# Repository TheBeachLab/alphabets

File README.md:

<!-- SPDX-FileCopyrightText: 2014-2026 The Beach Lab <https://beachlab.org> -->
<!-- SPDX-License-Identifier: MIT -->
# Alphabets

Welcome to the public repository of the second edition (**V2**) of Alphabets,
an open-source modular split-flap display. Each module shows one character, and
modules can be arranged together to display messages. For information about
the first release from 2014, see [V1](V1). Please also check the [YouTube videos](https://www.youtube.com/playlist?list=PLKDpiLmgp6EuLGCovD-QFxrmyNdrbUmKX)

## The two V2 versions

In this repository you will find two V2 versions: **V2 Prototype** and
**V2 Final**. They are complete, incompatible physical profiles; each has its
own stickers, cards, drum and enclosure, and their parts must not be mixed.

- **V2 Prototype** is for myself. A while ago I printed ten module sticker sets in Dubai and I am using those for prototyping. Of course might use those too. When new V2 Final sticker and card batches are available I will no longer develop this variant.
- **V2 Final** is the supported target for new batches. The expanded character
  map for the German-speaking DACH region (Germany, Austria and Switzerland)
  and Nordic languages requires more vertical artwork space, so this version
  uses taller stickers and cards with a matching drum and enclosure.

See the [V2 physical variants](V2/Hardware/variants/README.md) for the exact parts
and dimensions belonging to each version.

> [!WARNING]
> **UNDER HEAVY DEVELOPMENT — NOT READY FOR USE OR FABRICATION.**
> The V2 Final enclosure has a recorded print check, but the complete mechanism,
> Prototype enclosure, electronics and production process are not physically
> validated. Do not order, print, cut or assemble multiple parts without
> checking the dimensions and validating one complete module. Never mix files
> between the Prototype and Final folders.

## What's new in V2

* 120% pure awesomeness.
* 64 cards with international character set.
* Custom colors: Request custom colored modules and custom characters.
* Build your own or order a kit or ready built module.
* No more gears, direct drive motor
* 3D Printed enclosure
* Entirely designed with widely adopted open source software.
* Assemble in multiple layouts of rows and columns.
* Networked electronics: Connect from one to infinite(*) modules together.
* Web based interface: Control your modules interactively with your web browser.

(*) Not really

## TOC

This table of contents documents V2 Final.

- Mechanical
  - [Cards](doc/cards.md)
  - [Stickers](doc/stickers.md)
  - [Drum](doc/drum.md)
  - [Enclosure](doc/enclosure.md)
- Electronics
  - [Motors](doc/motors.md)
  - [Module Board](doc/module-board.md)
  - [Motherboard](doc/motherboard.md)
  - [Chaining and cables](doc/chaining-and-cables.md)
- Software and Architecture
  - [Protocol](doc/protocol.md)
  - [Module embedded software](doc/module-firmware.md)
  - [Motherboard embedded software](doc/motherboard-firmware.md)
  - [Web interface](doc/web-interface.md)

See the [documentation index](doc/README.md) for the same guide with the
current implementation status of each part.

## License

Except where a file or directory states otherwise, Alphabets' original source
code, firmware, electronics designs, mechanical designs, documentation, and
generated project artifacts are licensed under the [MIT License](LICENSE).
Copyright (c) 2014-2026 [The Beach Lab](https://beachlab.org).

Every commentable file carries a copyright and SPDX license header. JSON,
VS Code workspace, and native KiCad files embed the same fields as document
data so the declaration travels with them. Blender, FreeCAD, OpenType, SVG,
PDF, PNG, JPEG, ZIP, STEP, DXF, binary STL, Gerber, and Excellon files also use
embedded metadata or standard comments and do not need duplicate sidecars.
Only formats without a safely interoperable embedded mechanism use an adjacent
`.license` file. Legacy and bundled third-party sources retain their actual
notices and licenses.

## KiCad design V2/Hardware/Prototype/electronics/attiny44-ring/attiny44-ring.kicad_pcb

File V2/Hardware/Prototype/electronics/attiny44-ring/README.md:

<!-- SPDX-FileCopyrightText: 2014-2026 The Beach Lab <https://beachlab.org> -->
<!-- SPDX-License-Identifier: MIT -->
# Alphabets V2 ATtiny44 SPI-ring module

This directory contains the editable KiCad 10 design for one Alphabets V2
split-flap module. The ATtiny44 participates in the synchronous serial ring
defined in the [prototype module protocol](../../../../Protocol/PROTOCOL_V1_ATTINY44.md)
and drives the four
logic inputs of the external stepper-driver board supplied with the motor.
Its AVR C firmware is in
[`ATtiny44 module firmware`](../../../../Firmware/attiny44-module).

## Circuit

- `U1`: ATtiny44A-SS in SOIC-14.
- `J1`: one 2x3, 2.54 mm, surface-mount chain connector.
- `J5`: one standard 2x3, 2.54 mm, surface-mount AVR ISP connector placed
  immediately below `U1`.
- `J3`: four logic outputs for `IN1` through `IN4` on the external driver.
- `R2`: 10 kOhm reset pull-up in 1206.
- `C1`: 100 nF MCU decoupling capacitor in 1206.
- `C2`: 10 uF bulk capacitor in 1206.
- `JP5`, `JP6`, `JP7`, `JP8`, and `JP16` through `JP25`: 0 Ohm 1206 links
  used as physical copper bridges.

The ATtiny44 signal assignment follows the
[Microchip ATtiny24A/44A/84A data sheet](https://ww1.microchip.com/downloads/en/DeviceDoc/ATtiny24A-44A-84A-DataSheet-DS40002269A.pdf).

## Connectors

| Connector | Pinout |
| --- | --- |
| `J1 CHAIN` | 1 `LATCH`, 2 `CLOCK`, 3 `DATA_IN`, 4 `+5V`, 5 `DATA_OUT`, 6 `GND` |
| `J3 DRIVER` | 1 `IN1`, 2 `IN2`, 3 `IN3`, 4 `IN4` |
| `J5 ISP` | 1 `MISO`, 2 `+5V`, 3 `SCK`, 4 `MOSI`, 5 `RESET`, 6 `GND` |

The chain harness buses pins 1, 2, 4, and 6. It connects pin 5 of each module
to pin 3 of the following module. The external motor-driver board shares the
regulated 5 V supply and ground with this module.

`PB2/HOME` is unconnected on this PCB revision. The firmware uses an explicit
position-0 calibration command and persists completed positions in EEPROM.

## Milling rules

- Board outline: 50 x 50 mm.
- All routed copper is on `F.Cu`.
- Preferred tracks are 20 mil (0.508 mm); compact neckdowns remain 16 mil
  (0.4064 mm), never below the requested 15 mil minimum.
- Routed clearance is 0.40 mm for a 0.40 mm milling bit.
- Corners are native KiCad arcs fitted independently against DRC, trying radius
  limits from 2.00 mm down to 0.20 mm only where the 0.40 mm isolation requires
  it.
- Changes between 20 mil and 16 mil use curved 0.90 mm copper tapers; routed
  SMD pad entries use separate curved copper teardrops.
- Crossings use 0 Ohm 1206 links.
- All discrete SMD passives use 1206 footprints.
- `JP20` through `JP25` use the project-local compact-pitch 3216 crossover
  footprint so their pads fit between the adjacent milled traces.

## Files and validation

- `attiny44-ring.kicad_pro`, `.kicad_sch`, and `.kicad_pcb`: editable native
  KiCad project files.
- `fabrication/`: front-copper Gerbers, drill data, BOM, positions, and STEP.
- `preview/`: rendered top, copper, and schematic views.
- `validation/`: current ERC and DRC/schematic-parity reports.
- `tools/`: deterministic schematic, single-layer routing, organic post-process,
  and design checks.
- `third_party/`: the vendored, licensed geometry engines from
  [KiCad Round Tracks 1.6](https://github.com/mitxela/kicad-round-tracks/releases/tag/1.6)
  and [NilujePerchut's teardrop helper](https://github.com/NilujePerchut/kicad_scripts).

The workflow uses native files and command-line validation rather than GUI
automation. The checked-in Freerouting session reproduces the verified routing
deterministically. Set the KiCad paths, then run:

```sh
make schematic board route organic check fabrication previews
```

`make board route` is the easy-to-edit angular source. `make organic` creates
the fabrication board by fitting 20 mil tracks wherever DRC preserves the full
0.40 mm isolation, retaining 16 mil only where the compact layout requires it.
It then fits the largest safe radius at every corner, adds smooth width tapers
and curved SMD teardrops, and runs the normal ERC/DRC, fabrication, and preview
steps.

Use `make autoroute FREEROUTING_JAR=/path/to/freerouting.jar` only when the
placement or netlist changes and a new routing session must be explored.

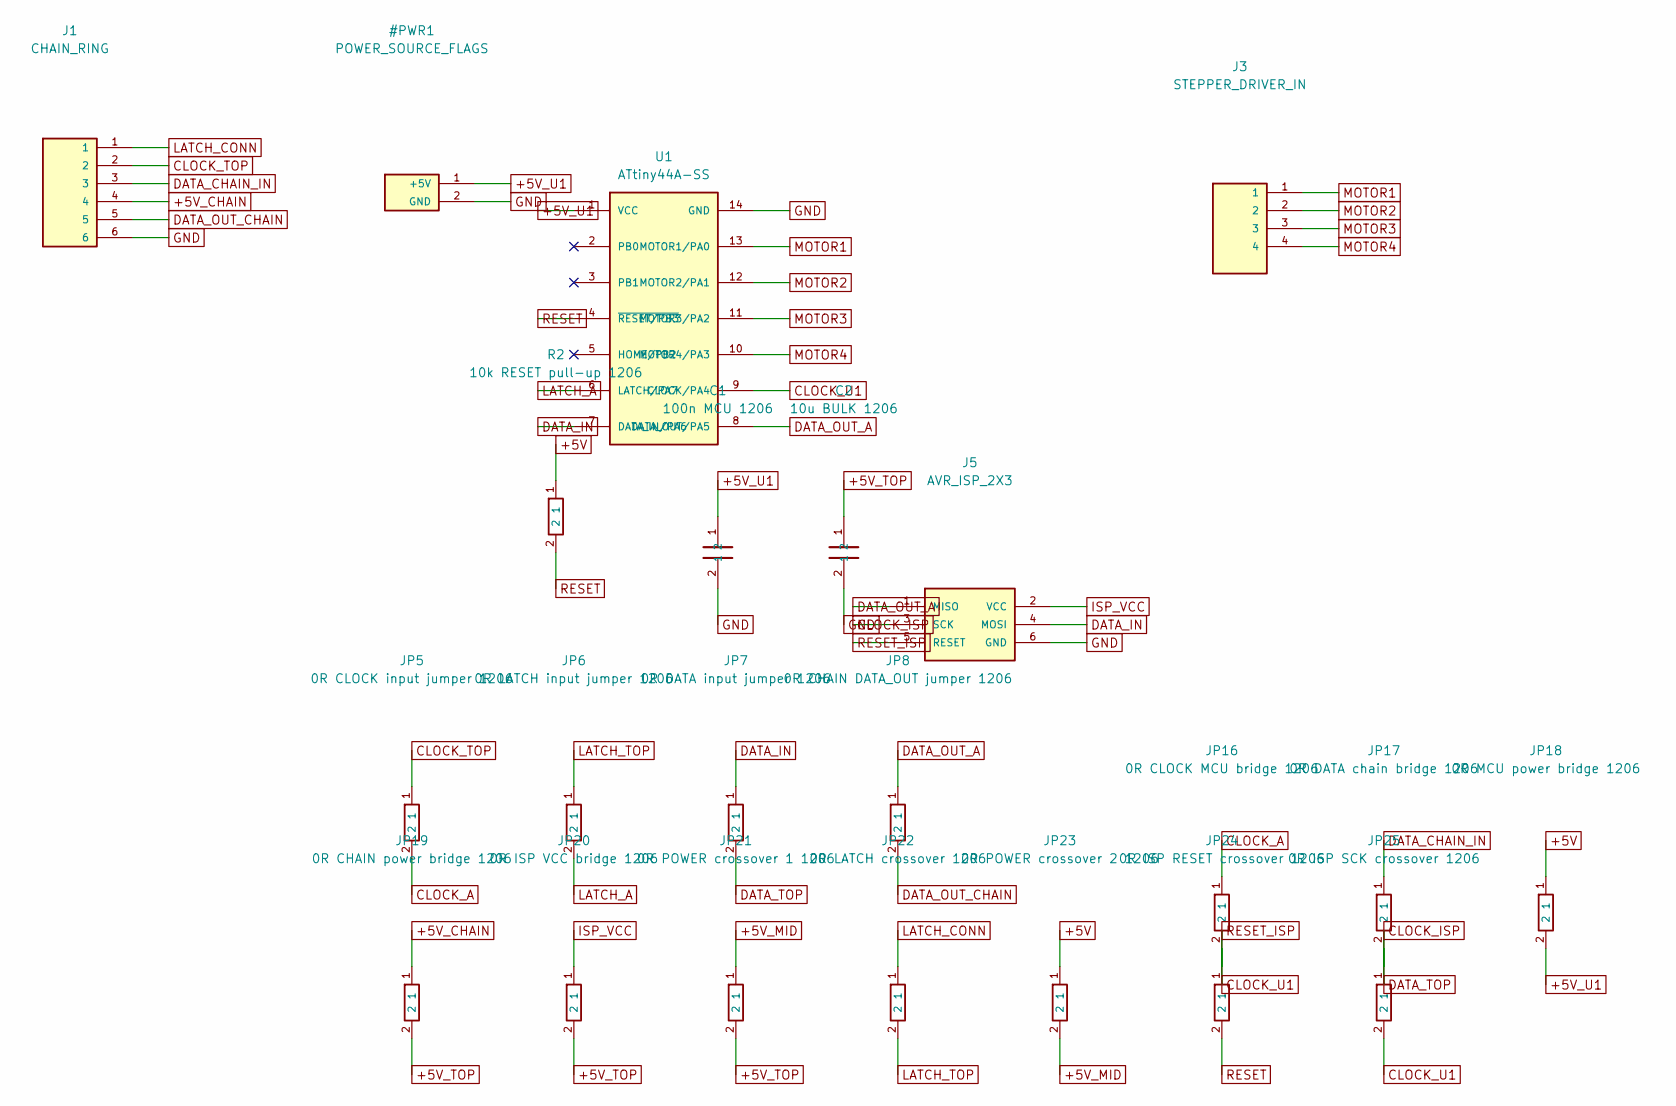
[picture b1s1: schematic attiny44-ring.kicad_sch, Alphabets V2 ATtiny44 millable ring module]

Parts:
C1: 100n MCU 1206; C_1206_3216Metric_Pad1.33x1.80mm_HandSolder
C2: 10u BULK 1206; C_1206_3216Metric_Pad1.33x1.80mm_HandSolder
J1: CHAIN_RING; PinHeader_2x03_P2.54mm_Vertical_SMD
J3: STEPPER_DRIVER_IN; PinHeader_1x04_P2.54mm_Vertical_SMD_Pin1Left
J5: AVR_ISP_2X3; PinHeader_2x03_P2.54mm_Vertical_SMD
JP5: 0R CLOCK input jumper 1206; R_1206_3216Metric_Pad1.30x1.75mm_HandSolder
JP6: 0R LATCH input jumper 1206; R_1206_3216Metric_Pad1.30x1.75mm_HandSolder
JP7: 0R DATA input jumper 1206; R_1206_3216Metric_Pad1.30x1.75mm_HandSolder
JP8: 0R CHAIN DATA_OUT jumper 1206; R_1206_3216Metric_Pad1.30x1.75mm_HandSolder
JP16: 0R CLOCK MCU bridge 1206; R_1206_3216Metric_Pad1.30x1.75mm_HandSolder
JP17: 0R DATA chain bridge 1206; R_1206_3216Metric_Pad1.30x1.75mm_HandSolder
JP18: 0R MCU power bridge 1206; R_1206_3216Metric_Pad1.30x1.75mm_HandSolder
JP19: 0R CHAIN power bridge 1206; R_1206_3216Metric_Pad1.30x1.75mm_HandSolder
JP20: 0R ISP VCC bridge 1206; R_1206_3216Metric_CompactCrossover
JP21: 0R POWER crossover 1 1206; R_1206_3216Metric_CompactCrossover
JP22: 0R LATCH crossover 1206; R_1206_3216Metric_CompactCrossover
JP23: 0R POWER crossover 2 1206; R_1206_3216Metric_CompactCrossover
JP24: 0R ISP RESET crossover 1206; R_1206_3216Metric_CompactCrossover
JP25: 0R ISP SCK crossover 1206; R_1206_3216Metric_CompactCrossover
R2: 10k RESET pull-up 1206; R_1206_3216Metric_Pad1.30x1.75mm_HandSolder
U1: ATtiny44A-SS; SOIC-14_3.9x8.7mm_P1.27mm

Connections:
+5V: JP18.1, JP23.1, R2.1
+5V_CHAIN: J1.4, JP19.1
+5V_MID: JP21.1, JP23.2
+5V_TOP: C2.1, JP19.2, JP20.2, JP21.2
CLOCK_A: JP5.2, JP16.1
CLOCK_ISP: J5.3 (SCK), JP25.1
CLOCK_TOP: J1.2, JP5.1
CLOCK_U1: JP16.2, JP25.2, U1.9 (CLOCK/PA4)
DATA_CHAIN_IN: J1.3, JP17.1
DATA_IN: J5.4 (MOSI), JP7.1, U1.7 (DATA_IN/PA6)
DATA_OUT_A: J5.1 (MISO), JP8.1, U1.8 (DATA_OUT/PA5)
DATA_OUT_CHAIN: J1.5, JP8.2
DATA_TOP: JP7.2, JP17.2
ISP_VCC: J5.2 (VCC), JP20.1
LATCH_A: JP6.2, U1.6 (LATCH/PA7)
LATCH_CONN: J1.1, JP22.1
LATCH_TOP: JP6.1, JP22.2
MOTOR1: J3.1, U1.13 (MOTOR1/PA0)
MOTOR2: J3.2, U1.12 (MOTOR2/PA1)
MOTOR3: J3.3, U1.11 (MOTOR3/PA2)
MOTOR4: J3.4, U1.10 (MOTOR4/PA3)
RESET: JP24.2, R2.2, U1.4 (~RESET/PB3)
RESET_ISP: J5.5 (RESET), JP24.1

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
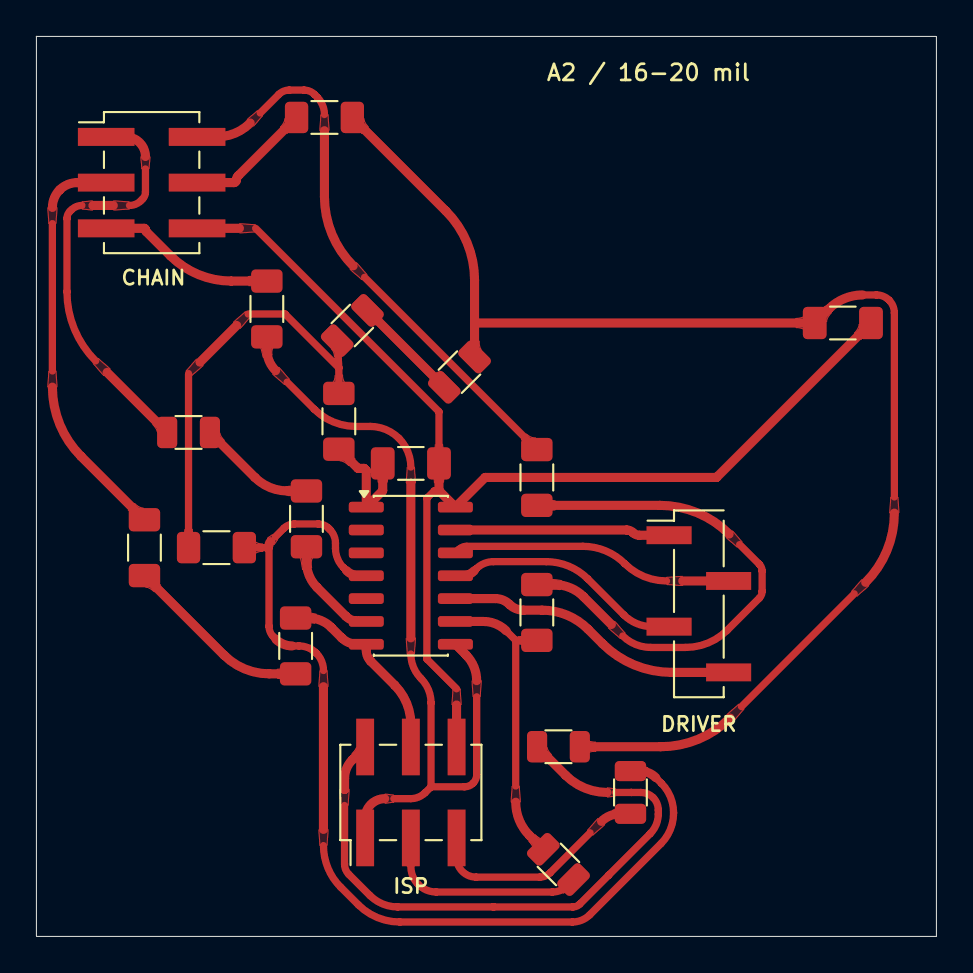
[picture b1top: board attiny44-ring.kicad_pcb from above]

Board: 2 copper layers, 50.0 x 50.0 mm, 21 parts (0 on the bottom side), 25 nets.

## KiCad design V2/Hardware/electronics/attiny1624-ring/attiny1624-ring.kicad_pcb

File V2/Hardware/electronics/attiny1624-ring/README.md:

<!-- SPDX-FileCopyrightText: 2014-2026 The Beach Lab <https://beachlab.org> -->
<!-- SPDX-License-Identifier: MIT -->
# Alphabets V2 ATtiny1624 ring module

This directory contains the editable KiCad 10 design for one Alphabets V2
split-flap module. The board keeps the existing 2x3 synchronous-ring connector,
drives an external four-input stepper board, reads a powered HOME sensor, and
uses the ATtiny1624's one-wire UPDI programming interface.

The hardware assignment follows Microchip's
[ATtiny1624/1626/1627 data sheet](https://ww1.microchip.com/downloads/en/DeviceDoc/ATtiny1624-26-27-DataSheet-DS40002234B.pdf).
Microchip documents PA0 as UPDI/RESET and PA1, PA2, and PA3 as SPI0 MOSI, MISO,
and SCK respectively. The standard programming connection is the 2x3,
2.54 mm UPDI header described in Microchip's
[UPDI connection guide](https://onlinedocs.microchip.com/oxy/GUID-ACE76F82-8072-410B-AFA7-16B2BF7B4CBA-en-US-8/GUID-C59C16EC-2784-4583-8198-2780FE485FFC.html).

## Circuit

- `U1`: ATtiny1624-SSU in SOIC-14.
- `J1`: 2x3 SMD ring connector for LATCH, CLOCK, serial data, +5 V, and GND.
- `J3`: four logic outputs for the external stepper driver.
- `J4`: powered three-pin HOME sensor connector with a 10 kOhm pull-up.
- `J5`: 2x3 SMD UPDI connector; pins 1, 2, and 6 carry UPDI, target VDD, and
  GND. Pins 3 through 5 are intentionally not connected.
- `R1`: 10 kOhm UPDI pull-up; `R2`: 10 kOhm HOME pull-up.
- `C1`: 100 nF local MCU decoupling; `C2`: 1 nF high-frequency bypass;
  `C3`: 10 uF board bulk capacitance.
- `JP1` through `JP4`, `JP6`, and `JP9`: removable 0 Ohm 1206
  links that partition power, ground, and ring signals for assembly and
  diagnosis.

The board defines this ATtiny1624 signal assignment:

| Function | MCU signal | Physical pin |
| --- | --- | ---: |
| VDD | `VDD` | 1 |
| LATCH | `PA4 / SPI0 SS` | 2 |
| HOME | `PA5` | 3 |
| Motor 4 | `PB3` | 6 |
| Motor 3 | `PB2` | 7 |
| Motor 2 | `PB1` | 8 |
| Motor 1 | `PB0` | 9 |
| UPDI | `PA0 / UPDI` | 10 |
| DATA_IN | `PA1 / SPI0 MOSI` | 11 |
| DATA_OUT | `PA2 / SPI0 MISO` | 12 |
| CLOCK | `PA3 / SPI0 SCK` | 13 |
| GND | `GND` | 14 |

`PA6` and `PA7` remain available and are intentionally not connected in this
revision. The matching firmware and host-side protocol tests are in
[`../../../Firmware/attiny1624-module`](../../../Firmware/attiny1624-module).

## Connectors

| Connector | Pinout |
| --- | --- |
| `J1 CHAIN` | 1 `LATCH`, 2 `CLOCK`, 3 `DATA_IN`, 4 `+5V`, 5 `DATA_OUT`, 6 `GND` |
| `J3 DRIVER` | 1 `MOTOR1`, 2 `MOTOR2`, 3 `MOTOR3`, 4 `MOTOR4` |
| `J4 HOME` | 1 `+5V`, 2 `HOME`, 3 `GND` |
| `J5 UPDI` | 1 `UPDI`, 2 target `VDD`, 3-5 NC, 6 `GND` |

The chain connector follows [`../../../PROTOCOL.md`](../../../PROTOCOL.md):
pins 1, 2, 4, and 6 are bused, while pin 5 of one module feeds pin 3 of the
next module.

## Single-sided construction

- Finished outline: 50 x 50 mm.
- All routed copper is on `F.Cu`; the design contains no vias or back-copper
  tracks.
- Preferred tracks are 20 mil (0.508 mm). Constrained neckdowns are 16 mil
  (0.4064 mm), above the 15 mil minimum.
- Copper clearance is 0.40 mm for a 0.40 mm milling tool.
- Corners use native KiCad arcs with adaptive radii from 0.20 to 2.00 mm.
- Width transitions use curved copper tapers and routed SMD entries use curved
  teardrops.
- Every discrete resistor and capacitor uses a hand-solderable 1206 footprint.

Ten insulated wire links cross above the routed copper. Solder insulated wire
between the two pads of each footprint; the dashed `F.Fab` line marks its
assembly path and is not copper:

| Reference | Signal | Pad spacing |
| --- | --- | ---: |
| `JP5` | CLOCK | 22.3 mm |
| `JP7` | DATA_IN | 25.6 mm |
| `JP8` | DATA_OUT | 23.5 mm |
| `JP10` | UPDI | 16.6 mm |
| `JP11` | chain GND | 29.7 mm |
| `JP12` | motor phase 3 | 23.5 mm |
| `JP13` | MCU power source | 17.7 mm |
| `JP14` | motor phase 1 | 30.3 mm |
| `JP15` | motor phase 2 | 24.5 mm |
| `JP16` | main power distribution | 27.0 mm |

## Files and reproducible validation

- `attiny1624-ring.kicad_pro`, `.kicad_sch`, and `.kicad_pcb`: editable
  native KiCad project files.
- `fabrication/`: Gerbers, drill outputs, BOM, positions, and STEP model.
- `preview/`: top render, front-copper drawing, and schematic drawing.
- `validation/`: ERC and DRC/schematic-parity reports.
- `routing/attiny1624-ring.ses`: checked-in single-layer routing session.
- `tools/`: deterministic generators, route import, organic post-processing,
  and project-specific electrical/mechanical checks.

The normal reproducible path starts from the checked-in route:

```sh
make schematic board route organic check fabrication previews
```

Set `KICAD_CLI`, `KICAD_PYTHON`, `KIUTILS_PYTHON`, and
`KICAD10_FOOTPRINT_DIR` for the installed KiCad environment. When placement or
the netlist changes, create a new session with:

```sh
make autoroute FREEROUTING_JAR=/path/to/freerouting.jar
```

`make check` enforces the 50 x 50 mm outline, front-copper-only routing, zero
vias, 16/20 mil widths, ten wire links, native arcs, teardrops, zero ERC/DRC
violations, zero unrouted connections, and exact schematic-to-PCB parity.

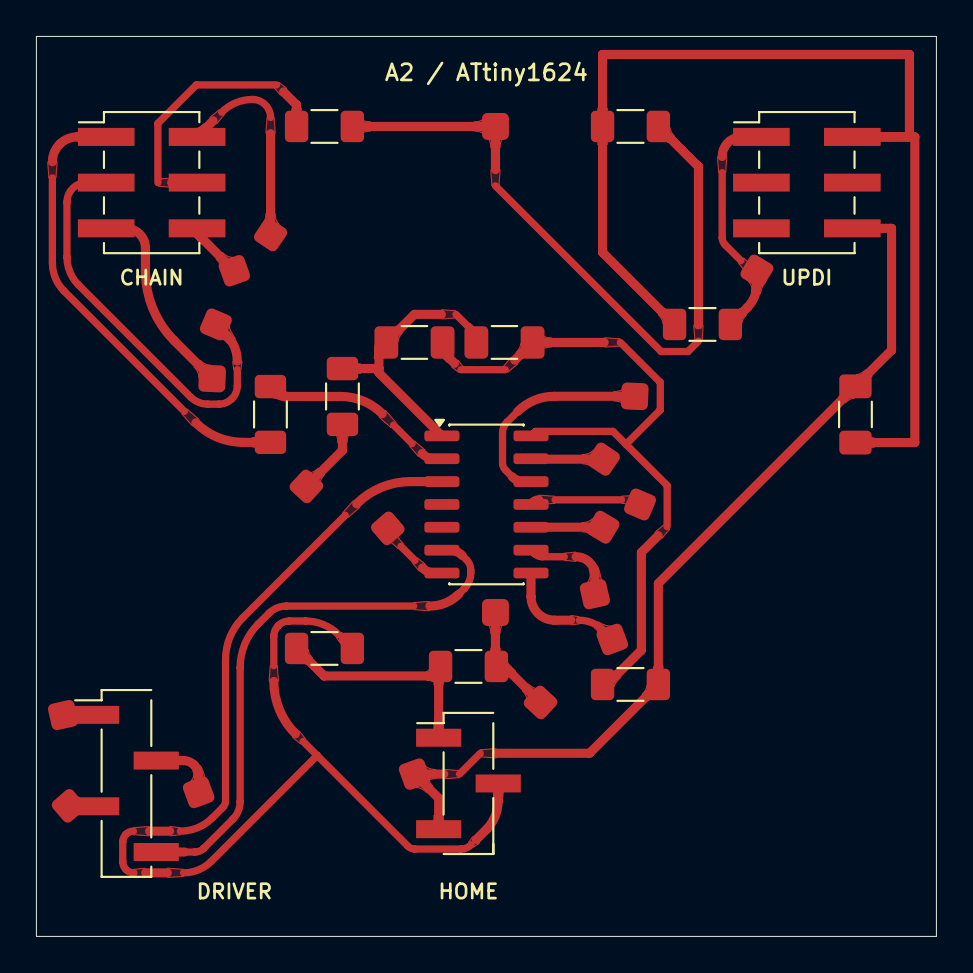
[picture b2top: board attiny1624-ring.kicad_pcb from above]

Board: 2 copper layers, 50.0 x 50.0 mm, 26 parts (0 on the bottom side), 28 nets.

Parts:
C1: 100n MCU 1206; C_1206_3216Metric_Pad1.33x1.80mm_HandSolder
C2: 1n HF 1206; C_1206_3216Metric_Pad1.33x1.80mm_HandSolder
C3: 10u BULK 1206; C_1206_3216Metric_Pad1.33x1.80mm_HandSolder
J1: CHAIN_RING; PinHeader_2x03_P2.54mm_Vertical_SMD
J3: STEPPER_DRIVER_IN; PinHeader_1x04_P2.54mm_Vertical_SMD_Pin1Left
J4: HOME_SENSOR; PinHeader_1x03_P2.54mm_Vertical_SMD_Pin1Left
J5: UPDI_2X3; PinHeader_2x03_P2.54mm_Vertical_SMD
JP1: 0R CHAIN power bridge 1206; R_1206_3216Metric_Pad1.30x1.75mm_HandSolder
JP2: 0R UPDI power bridge 1206; R_1206_3216Metric_Pad1.30x1.75mm_HandSolder
JP3: 0R HOME power bridge 1206; R_1206_3216Metric_Pad1.30x1.75mm_HandSolder
JP4: 0R MCU power bridge 1206; R_1206_3216Metric_Pad1.30x1.75mm_HandSolder
JP5: INSULATED CLOCK LINK 22.3mm; WireLink_22.3mm_SMD
JP6: 0R LATCH bridge 1206; R_1206_3216Metric_Pad1.30x1.75mm_HandSolder
JP7: INSULATED DATA_IN LINK 25.6mm; WireLink_25.6mm_SMD
JP8: INSULATED DATA_OUT LINK 23.5mm; WireLink_23.5mm_SMD
JP9: 0R MCU ground bridge 1206; R_1206_3216Metric_Pad1.30x1.75mm_HandSolder
JP10: INSULATED UPDI LINK 16.6mm; WireLink_16.6mm_SMD
JP11: INSULATED GND LINK 29.7mm; WireLink_29.7mm_SMD
JP12: INSULATED MOTOR3 LINK 23.5mm; WireLink_23.5mm_SMD
JP13: INSULATED MCU POWER LINK 17.7mm; WireLink_17.7mm_SMD
JP14: INSULATED MOTOR1 LINK 30.3mm; WireLink_30.3mm_SMD
JP15: INSULATED MOTOR2 LINK 24.5mm; WireLink_24.5mm_SMD
JP16: INSULATED MAIN POWER LINK 27.0mm; WireLink_27.0mm_SMD
R1: 10k UPDI pull-up 1206; R_1206_3216Metric_Pad1.30x1.75mm_HandSolder
R2: 10k HOME pull-up 1206; R_1206_3216Metric_Pad1.30x1.75mm_HandSolder
U1: ATtiny1624-SSU; SOIC-14_3.9x8.7mm_P1.27mm

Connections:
+5V_CHAIN: J1.4, JP1.1
+5V_HOME: J4.1, JP3.1, R2.1
+5V_MAIN: JP3.2, JP13.1, JP16.2
+5V_MAIN_TOP: JP1.2, JP2.2, JP16.1
+5V_MCU_SOURCE: JP4.1, JP13.2
+5V_U1: C1.1, C2.1, JP4.2, U1.1
+5V_UPDI: C3.1, J5.2, JP2.1, R1.1
CLOCK_CONN: J1.2, JP5.1
CLOCK_U1: JP5.2, U1.13
DATA_CHAIN_IN: J1.3, JP7.1
DATA_IN_U1: JP7.2, U1.11
DATA_OUT_CHAIN: J1.5, JP8.2
DATA_OUT_U1: JP8.1, U1.12
GND: C3.2, J4.3, J5.6, JP9.2, JP11.2
GND_CHAIN: J1.6, JP11.1
GND_U1: C1.2, C2.2, JP9.1, U1.14
HOME: J4.2, R2.2, U1.3
LATCH_CONN: J1.1, JP6.1
LATCH_U1: JP6.2, U1.2
MOTOR1_DRIVER: J3.1, JP14.2
MOTOR1_U1: JP14.1, U1.9
MOTOR2_DRIVER: J3.2, JP15.2
MOTOR2_U1: JP15.1, U1.8
MOTOR3_DRIVER: J3.3, JP12.2
MOTOR3_U1: JP12.1, U1.7
MOTOR4: J3.4, U1.6
UPDI_PROG: J5.1, JP10.1, R1.2
UPDI_U1: JP10.2, U1.10

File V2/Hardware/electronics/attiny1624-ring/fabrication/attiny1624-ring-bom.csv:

"Refs","Value","Footprint","Qty"
"C1","100n MCU 1206","Capacitor_SMD:C_1206_3216Metric_Pad1.33x1.80mm_HandSolder","1"
"C2","1n HF 1206","Capacitor_SMD:C_1206_3216Metric_Pad1.33x1.80mm_HandSolder","1"
"C3","10u BULK 1206","Capacitor_SMD:C_1206_3216Metric_Pad1.33x1.80mm_HandSolder","1"
"J1","CHAIN_RING","Connector_PinHeader_2.54mm:PinHeader_2x03_P2.54mm_Vertical_SMD","1"
"J3","STEPPER_DRIVER_IN","Connector_PinHeader_2.54mm:PinHeader_1x04_P2.54mm_Vertical_SMD_Pin1Left","1"
"J4","HOME_SENSOR","Connector_PinHeader_2.54mm:PinHeader_1x03_P2.54mm_Vertical_SMD_Pin1Left","1"
"J5","UPDI_2X3","Connector_PinHeader_2.54mm:PinHeader_2x03_P2.54mm_Vertical_SMD","1"
"JP1","0R CHAIN power bridge 1206","Resistor_SMD:R_1206_3216Metric_Pad1.30x1.75mm_HandSolder","1"
"JP2","0R UPDI power bridge 1206","Resistor_SMD:R_1206_3216Metric_Pad1.30x1.75mm_HandSolder","1"
"JP3","0R HOME power bridge 1206","Resistor_SMD:R_1206_3216Metric_Pad1.30x1.75mm_HandSolder","1"
"JP4","0R MCU power bridge 1206","Resistor_SMD:R_1206_3216Metric_Pad1.30x1.75mm_HandSolder","1"
"JP5","INSULATED CLOCK LINK 22.3mm","Alphabets:WireLink_22.3mm_SMD","1"
"JP6","0R LATCH bridge 1206","Resistor_SMD:R_1206_3216Metric_Pad1.30x1.75mm_HandSolder","1"
"JP7","INSULATED DATA_IN LINK 25.6mm","Alphabets:WireLink_25.6mm_SMD","1"
"JP8","INSULATED DATA_OUT LINK 23.5mm","Alphabets:WireLink_23.5mm_SMD","1"
"JP9","0R MCU ground bridge 1206","Resistor_SMD:R_1206_3216Metric_Pad1.30x1.75mm_HandSolder","1"
"JP10","INSULATED UPDI LINK 16.6mm","Alphabets:WireLink_16.6mm_SMD","1"
"JP11","INSULATED GND LINK 29.7mm","Alphabets:WireLink_29.7mm_SMD","1"
"JP12","INSULATED MOTOR3 LINK 23.5mm","Alphabets:WireLink_23.5mm_SMD","1"
"JP13","INSULATED MCU POWER LINK 17.7mm","Alphabets:WireLink_17.7mm_SMD","1"
"JP14","INSULATED MOTOR1 LINK 30.3mm","Alphabets:WireLink_30.3mm_SMD","1"
"JP15","INSULATED MOTOR2 LINK 24.5mm","Alphabets:WireLink_24.5mm_SMD","1"
"JP16","INSULATED MAIN POWER LINK 27.0mm","Alphabets:WireLink_27.0mm_SMD","1"
"R1","10k UPDI pull-up 1206","Resistor_SMD:R_1206_3216Metric_Pad1.30x1.75mm_HandSolder","1"
"R2","10k HOME pull-up 1206","Resistor_SMD:R_1206_3216Metric_Pad1.30x1.75mm_HandSolder","1"
"U1","ATtiny1624-SSU","Package_SO:SOIC-14_3.9x8.7mm_P1.27mm","1"

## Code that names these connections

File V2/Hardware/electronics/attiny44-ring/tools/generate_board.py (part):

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    "MOTOR4",
    "unconnected-(U1-PB0-Pad2)",
    "unconnected-(U1-PB1-Pad3)",
    "unconnected-(U1-HOME{slash}PB2-Pad5)",
]


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

PARTS = [
    ("J1", "Connector_PinHeader_2.54mm", "PinHeader_2x03_P2.54mm_Vertical_SMD", "CHAIN_RING", (105.4, 108.12), 0, {"1": "LATCH_CONN", "2": "CLOCK_TOP", "3": "DATA_CHAIN_IN", "4": "+5V_CHAIN", "5": "DATA_OUT_CHAIN", "6": "GND"}),
    ("J3", "Connector_PinHeader_2.54mm", "PinHeader_1x04_P2.54mm_Vertical_SMD_Pin1Left", "STEPPER_DRIVER_IN", (135.8, 131.52), 0, {"1": "MOTOR1", "2": "MOTOR2", "3": "MOTOR3", "4": "MOTOR4"}),
    ("J5", "Connector_PinHeader_2.54mm", "PinHeader_2x03_P2.54mm_Vertical_SMD", "AVR_ISP_2X3", (119.8, 142.0), 90, {"1": "DATA_OUT_A", "2": "ISP_VCC", "3": "CLOCK_U1", "4": "DATA_IN", "5": "RESET", "6": "GND"}),
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    ("R2", "Resistor_SMD", "R_1206_3216Metric_Pad1.30x1.75mm_HandSolder", "10k RESET pull-up 1206", (109.0, 128.4), 0, {"1": "+5V", "2": "RESET"}),
    ("C1", "Capacitor_SMD", "C_1206_3216Metric_Pad1.33x1.80mm_HandSolder", "100n MCU 1206", (119.8, 123.72), 0, {"1": "+5V_U1", "2": "GND"}),
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
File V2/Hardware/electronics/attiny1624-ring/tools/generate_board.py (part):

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    "unconnected-(J5-NC-Pad3)",
    "unconnected-(J5-NC-Pad4)",
    "unconnected-(J5-NC-Pad5)",
    "unconnected-(U1-PA6-Pad4)",
    "unconnected-(U1-PA7-Pad5)",
]


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

PARTS = [
    ("J1", "Connector_PinHeader_2.54mm", "PinHeader_2x03_P2.54mm_Vertical_SMD", "CHAIN_RING", (105.4, 108.12), 0, {"1": "LATCH_CONN", "2": "CLOCK_CONN", "3": "DATA_CHAIN_IN", "4": "+5V_CHAIN", "5": "DATA_OUT_CHAIN", "6": "GND_CHAIN"}),
    ("J3", "Connector_PinHeader_2.54mm", "PinHeader_1x04_P2.54mm_Vertical_SMD_Pin1Left", "STEPPER_DRIVER_IN", (104.0, 141.5), 0, {"1": "MOTOR1_DRIVER", "2": "MOTOR2_DRIVER", "3": "MOTOR3_DRIVER", "4": "MOTOR4"}),
    ("J4", "Connector_PinHeader_2.54mm", "PinHeader_1x03_P2.54mm_Vertical_SMD_Pin1Left", "HOME_SENSOR", (123.0, 141.5), 0, {"1": "+5V_HOME", "2": "HOME", "3": "GND"}),
    ("J5", "Connector_PinHeader_2.54mm", "PinHeader_2x03_P2.54mm_Vertical_SMD", "UPDI_2X3", (141.8, 108.12), 0, {"1": "UPDI_PROG", "2": "+5V_UPDI", "3": "unconnected-(J5-NC-Pad3)", "4": "unconnected-(J5-NC-Pad4)", "5": "unconnected-(J5-NC-Pad5)", "6": "GND"}),
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    ("R1", "Resistor_SMD", "R_1206_3216Metric_Pad1.30x1.75mm_HandSolder", "10k UPDI pull-up 1206", (136.0, 116.0), 0, {"1": "+5V_UPDI", "2": "UPDI_PROG"}),
    ("R2", "Resistor_SMD", "R_1206_3216Metric_Pad1.30x1.75mm_HandSolder", "10k HOME pull-up 1206", (115.0, 134.0), 0, {"1": "+5V_HOME", "2": "HOME"}),
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
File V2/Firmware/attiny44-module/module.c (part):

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
static void configure_io(void)
{
    DDRA = (DDRA & (uint8_t)~(_BV(PA4) | _BV(PA6) | _BV(PA7)))
        | MOTOR_MASK | _BV(PA5);
    PORTA &= (uint8_t)~(
        MOTOR_MASK | _BV(PA4) | _BV(PA5) | _BV(PA6) | _BV(PA7)
    );

    DDRB &= (uint8_t)~_BV(PB2);
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
static void configure_latch_interrupt(void)
{
    latch_was_high = (PINA & _BV(PA7)) != 0u;
    GIFR = _BV(PCIF0);
    PCMSK0 = _BV(PCINT7);
    GIMSK |= _BV(PCIE0);
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
ISR(PCINT0_vect)
{
    const bool latch_is_high = (PINA & _BV(PA7)) != 0u;

    if (latch_is_high == latch_was_high) {
        return;
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
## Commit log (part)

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2014-06-18 Added project folders and web link
2014-06-18 Added code, mechanics and electronics
2014-09-23 Added Split Flap letters
2014-09-24 Mechanical updates
2014-10-02 Maker Faire Rome Day 0
2014-10-02 Changes in lock
    Made it solid because breaks easily. Also increased length by 1 mm
    because some cards get stuck
2014-10-02 Updated gears file to show the 3 gears
2014-10-02 Added arduino code for one full revolution
2014-10-03 Day one changes
2014-10-03 John Rees is back
2014-10-03 Moving one by one version
2014-10-03 Simultaneus code. Unknown functionality
2014-10-03 Versions explained
2014-10-03 Rearranged folders
2014-10-04 Working version of all moving
2014-10-04 Working accelstepper version
2014-10-04 Changed delay
2014-10-04 Added John Rees script for displaying time
2014-10-05 ruby time updates
2014-10-05 code updates
2014-10-05 removed tabs
2014-10-05 email counter
2014-10-05 Fixed coordinates of the axis
2014-10-05 Added mount holes for a standard NEMA17 motor
2014-12-10 Removed old SVGs
2014-12-16 Preparing for version 2
2014-12-26 Universal letter version and 40 cards cut file
2014-12-26 Fixed W character. Working on V2 wheels
2015-05-25 WIP ew cardboard enclosure
2015-09-05 Changed documentation link
2015-10-05 Added kokopelli retro
2016-09-28 recovered part of the doc
2017-02-12 going kicked
2017-02-12 added video links
2017-02-12 starting port to freecad
2018-01-13 kickstarter panel
2018-01-16 multiple panel layouts
2018-01-17 hello alphabets
2018-01-17 fixing readme
2018-12-06 2018 changes
2019-01-14 linting
2019-01-16 recovered some V1 images
2019-02-14 3d printed spool
2020-01-26 removed xyz domain
2025-11-18 Change to TBL laser
2025-11-18 prepare to create new enclosure
2025-11-19 fix card extrude and prepare new enclosure
